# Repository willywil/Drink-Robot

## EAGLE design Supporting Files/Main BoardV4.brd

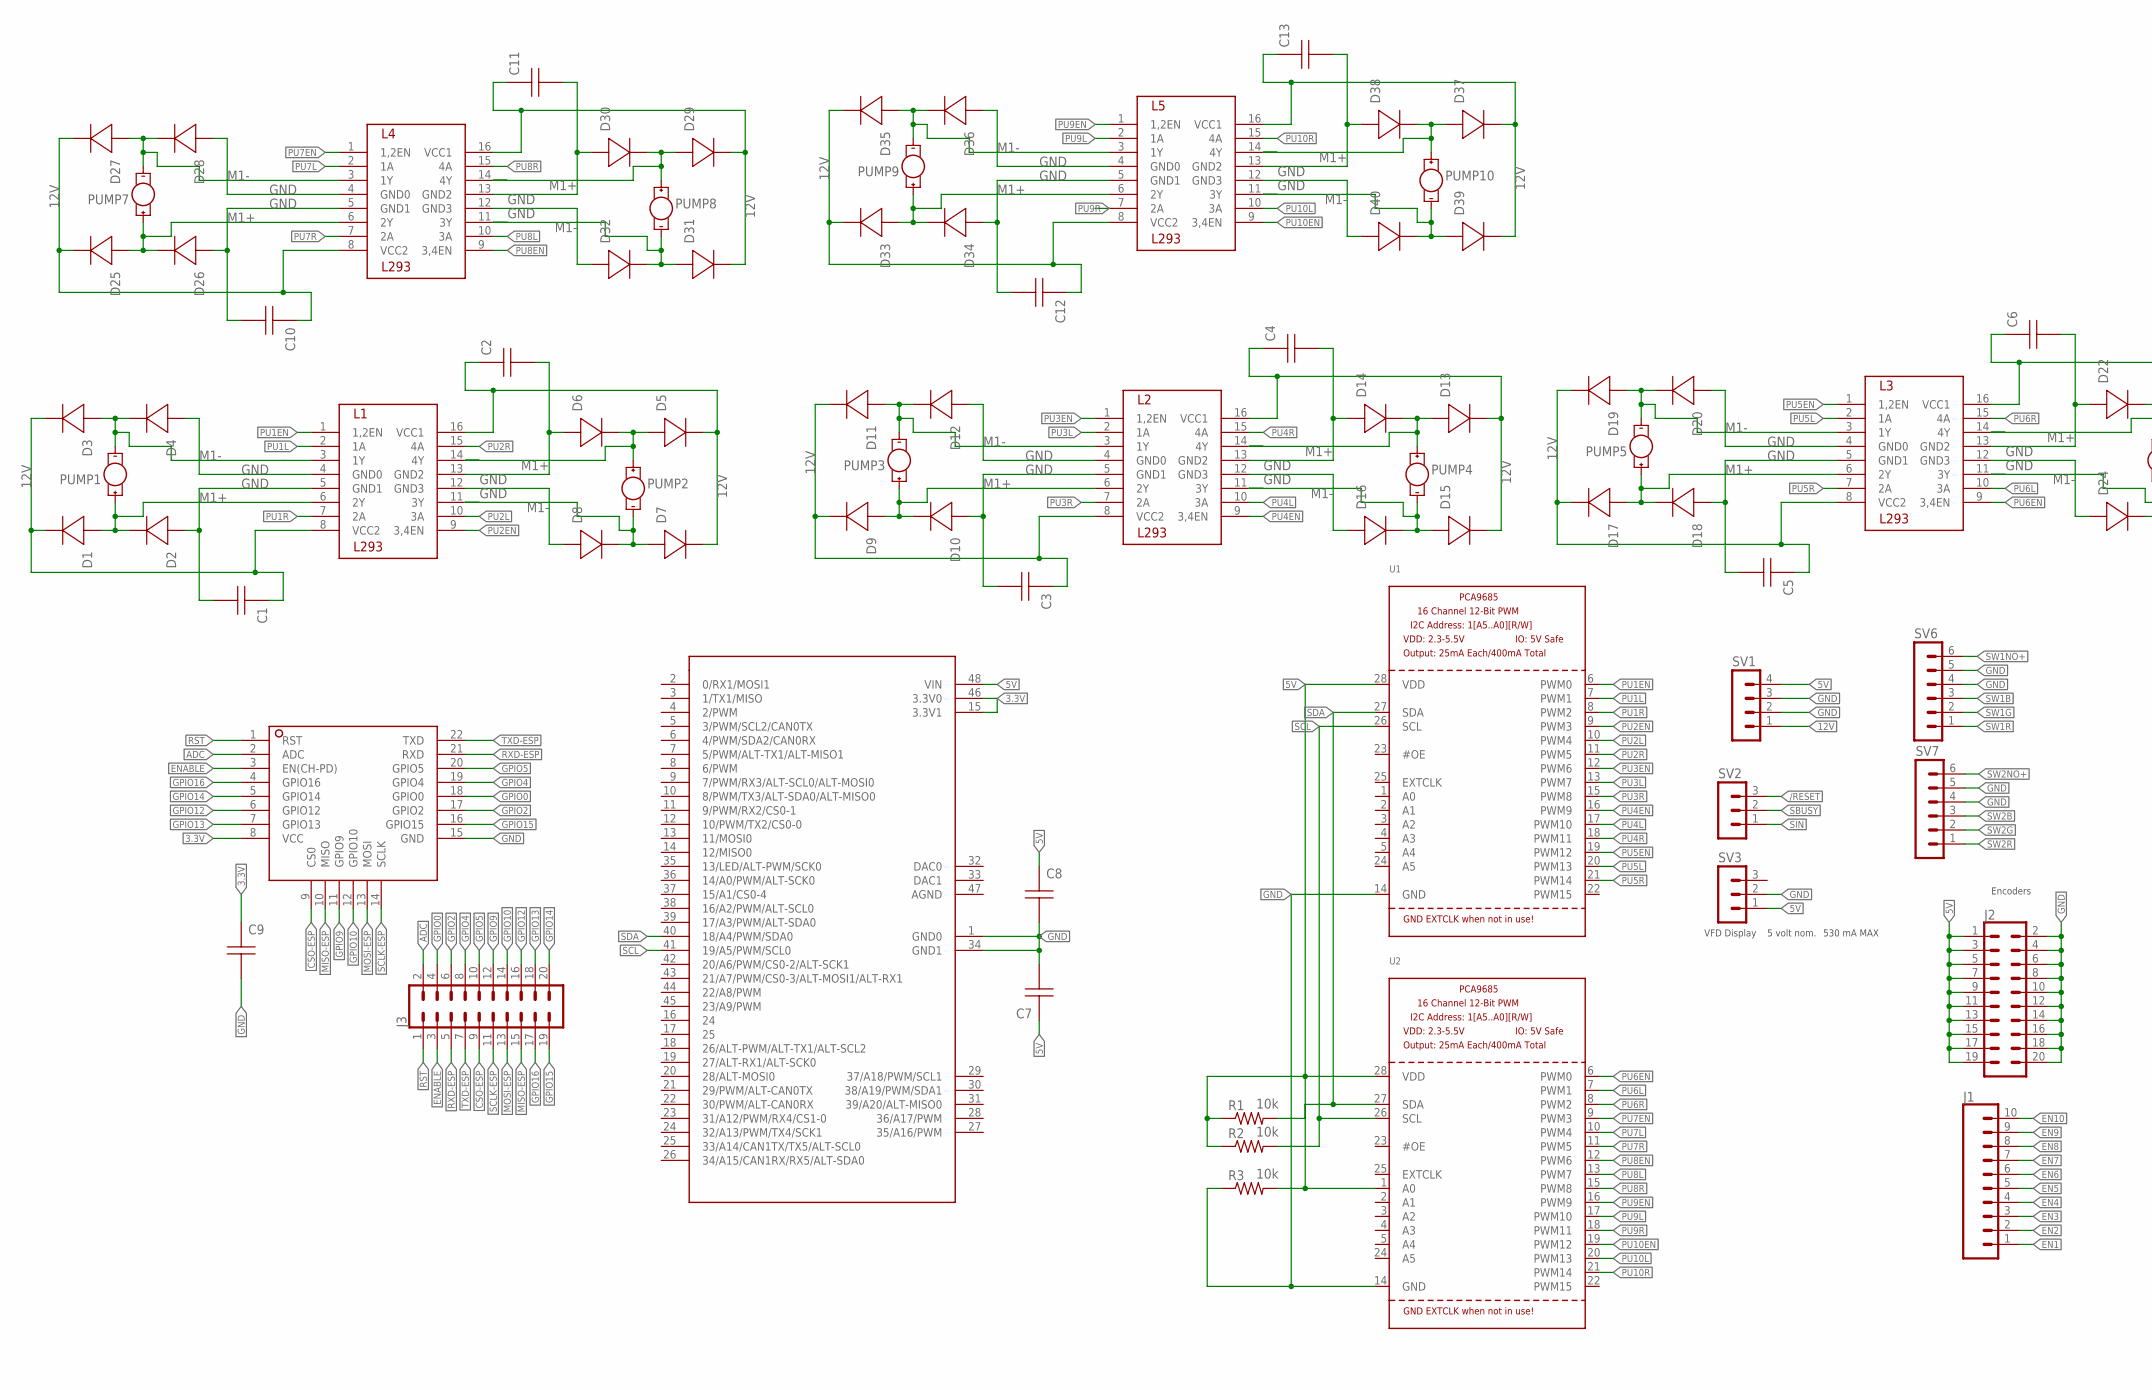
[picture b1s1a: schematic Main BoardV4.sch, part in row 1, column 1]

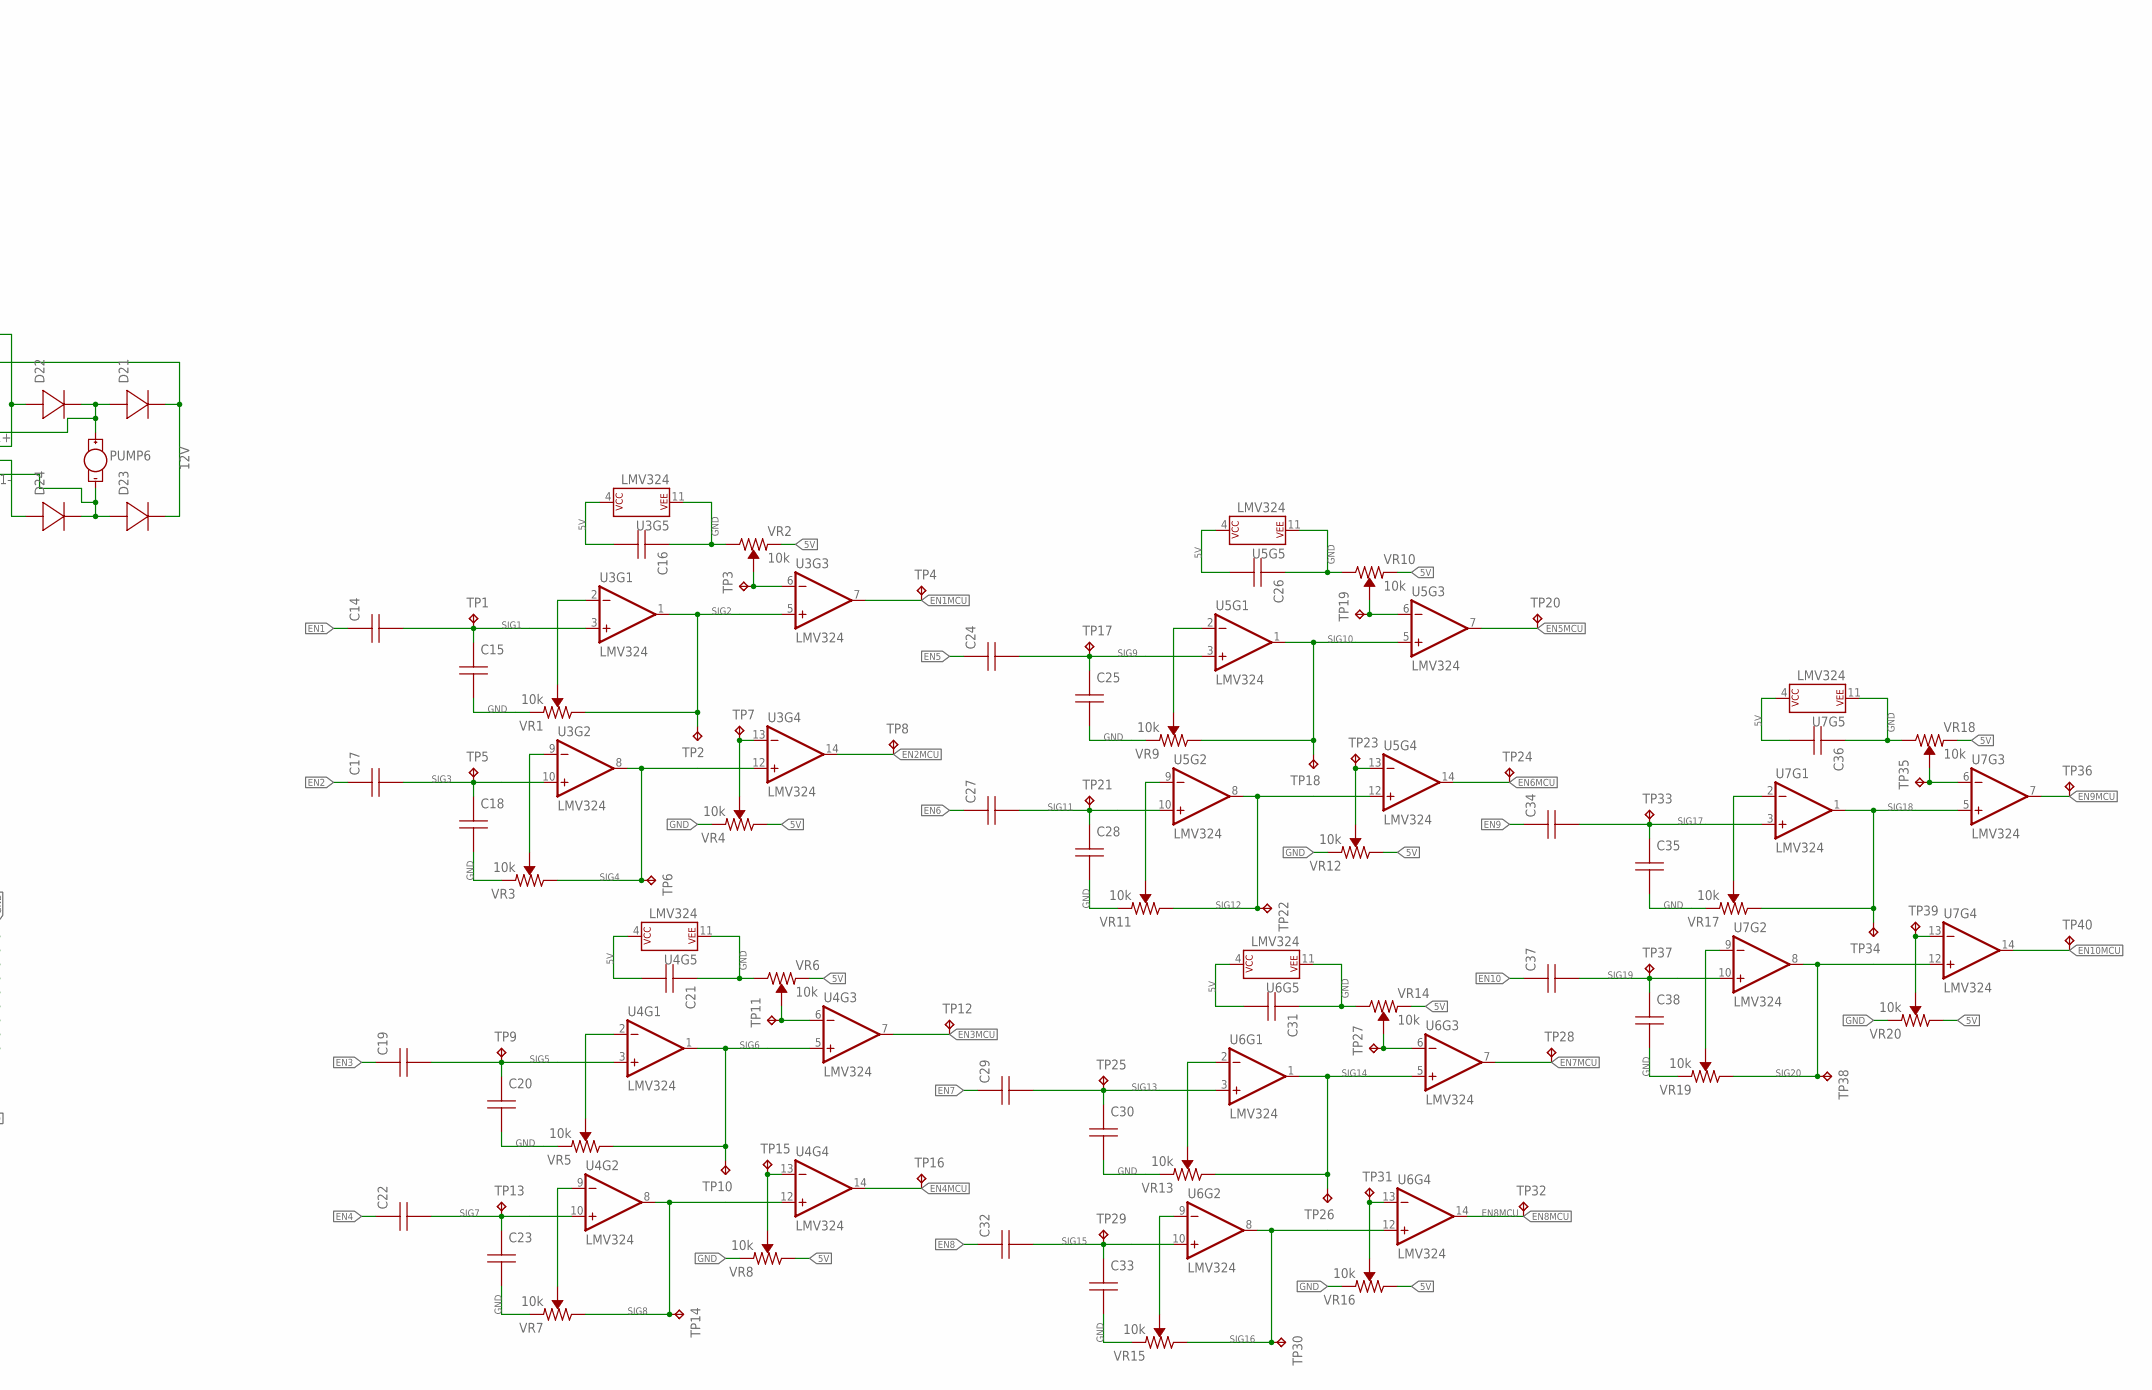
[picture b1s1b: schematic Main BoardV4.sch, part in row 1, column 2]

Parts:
C1, C2, C3, C4, C5, C6, C7, C8, C9, C10, C11, C12, C13, C14, C15, C16, C17, C18, C19, C20, C21, C22, C23, C24, C25, C26, C27, C28, C29, C30, C31, C32, C33, C34, C35, C36, C37, C38: CAP; C0805
D1, D2, D3, D4, D5, D6, D7, D8, D9, D10, D11, D12, D13, D14, D15, D16, D17, D18, D19, D20, D21, D22, D23, D24, D25, D26, D27, D28, D29, D30, D31, D32, D33, D34, D35, D36, D37, D38, D39, D40: UPR5E3-DIODE; DIOC4519X114
ESP1: ESP8266; ESP8266MOD
J1: CONN_10NO_SILK_PTH_FEMALE; 1X10_NO_SILK
J2: CONN_10X2NOSILK; 2X10_NOSILK
J3: CONN_10X22X10_LOCK; 2X10_LOCK
L1, L2, L3, L4, L5: L293; DIP762W53P254L1969H508Q16B
PUMP1, PUMP2, PUMP3, PUMP4, PUMP5, PUMP6, PUMP7, PUMP8, PUMP9, PUMP10: PUMPS; 1X2_HEADER
R1, R2, R3: 10k; R0402
SV1: MA04-1
SV2, SV3: MA03-1
SV6, SV7: MA06-1
TEENSY1: TEENSY_3.5; DIP1524W60P254L6350H635Q48A
TP1, TP2, TP3, TP4, TP5, TP6, TP7, TP8, TP9, TP10, TP11, TP12, TP13, TP14, TP15, TP16, TP17, TP18, TP19, TP20, TP21, TP22, TP23, TP24, TP25, TP26, TP27, TP28, TP29, TP30, TP31, TP32, TP33, TP34, TP35, TP36, TP37, TP38, TP39, TP40: TPPAD1-13; P1-13
U1, U2: PCA9685; TSSOP28
U3, U4, U5, U6, U7: LMV324; SO14
VR1, VR2, VR3, VR4, VR5, VR6, VR7, VR8, VR9, VR10, VR11, VR12, VR13, VR14, VR15, VR16, VR17, VR18, VR19, VR20: 10k; TRIMPOT-SMD-TC33X

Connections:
/RESET: SV2.3, TEENSY1.22 (30/PWM/ALT-CAN0RX)
ADC: ESP1.2 (ADC), J3.2
CSO-ESP: ESP1.9 (CS0), J3.9, TEENSY1.12 (10/PWM/TX2/CS0-0)
EN1: C14.1 (A), J1.1
EN1MCU: TEENSY1.36 (14/A0/PWM/ALT-SCK0), TP4.TP, U3.7 (OUT)
EN2: C17.1 (A), J1.2
EN2MCU: TEENSY1.37 (15/A1/CS0-4), TP8.TP, U3.14 (OUT)
EN3: C19.1 (A), J1.3
EN3MCU: TEENSY1.38 (16/A2/PWM/ALT-SCL0), TP12.TP, U4.7 (OUT)
EN4: C22.1 (A), J1.4
EN4MCU: TEENSY1.39 (17/A3/PWM/ALT-SDA0), TP16.TP, U4.14 (OUT)
EN5: C24.1 (A), J1.5
EN6: C27.1 (A), J1.6
EN7: C29.1 (A), J1.7
EN7MCU: TEENSY1.42 (20/A6/PWM/CS0-2/ALT-SCK1), TP28.TP, U6.7 (OUT)
EN8: C32.1 (A), J1.8
EN8MCU: TEENSY1.43 (21/A7/PWM/CS0-3/ALT-MOSI1/ALT-RX1), TP32.TP, U6.14 (OUT)
EN9: C34.1 (A), J1.9
EN9MCU: TEENSY1.44 (22/A8/PWM), TP36.TP, U7.7 (OUT)
EN10: C37.1 (A), J1.10
EN10MCU: TEENSY1.45 (23/A9/PWM), TP40.TP, U7.14 (OUT)
EN-WIFI: TEENSY1.24 (32/A13/PWM/TX4/SCK1); also elsewhere on the board
ENABLE: ESP1.3 (EN(CH-PD)), J3.3, TEENSY1.20 (28/ALT-MOSI0)
GND: C1.2 (B), C2.2 (B), C3.2 (B), C4.2 (B), C5.2 (B), C6.2 (B), C7.2 (B), C8.2 (B), C9.2 (B), C10.2 (B), C11.2 (B), C12.2 (B), C13.2 (B), C15.2 (B), C16.1 (A), C18.2 (B), C20.2 (B), C21.1 (A), C23.2 (B), C25.2 (B), C26.1 (A), C28.2 (B), C30.2 (B), C31.1 (A), C33.2 (B), C35.2 (B), C36.1 (A), C38.2 (B), D2.2 (+), D4.2 (+), D6.2 (+), D8.2 (+), D10.2 (+), D12.2 (+), D14.2 (+), D16.2 (+), D18.2 (+), D20.2 (+), D22.2 (+), D24.2 (+), D26.2 (+), D28.2 (+), D30.2 (+), D32.2 (+), D34.2 (+), D36.2 (+), D38.2 (+), D40.2 (+), ESP1.15 (GND), J2.2, J2.4, J2.6, J2.8, J2.10, J2.12, J2.14, J2.16, J2.18, J2.20, L1.4 (GND0), L1.5 (GND1), L1.12 (GND3), L1.13 (GND2), L2.4 (GND0), L2.5 (GND1), L2.12 (GND3), L2.13 (GND2), L3.4 (GND0), L3.5 (GND1), L3.12 (GND3), L3.13 (GND2), L4.4 (GND0), L4.5 (GND1), L4.12 (GND3), L4.13 (GND2), L5.4 (GND0), L5.5 (GND1), L5.12 (GND3), L5.13 (GND2), R3.1, SV1.2, SV1.3, SV3.2, SV6.4, SV6.5, SV7.4, SV7.5, TEENSY1.1 (GND0), TEENSY1.34 (GND1), U1.14 (GND), U2.14 (GND), U3.11 (P$V-), U4.11 (P$V-), U5.11 (P$V-), U6.11 (P$V-), U7.11 (P$V-), VR1.3 (CCW), VR2.1 (CW), VR3.3 (CCW), VR4.3 (CCW), VR5.3 (CCW), VR6.1 (CW), VR7.3 (CCW), VR8.3 (CCW), VR9.3 (CCW), VR10.1 (CW), VR11.3 (CCW), VR12.3 (CCW), VR13.3 (CCW), VR14.1 (CW), VR15.3 (CCW), VR16.3 (CCW), VR17.3 (CCW), VR18.1 (CW), VR19.3 (CCW), VR20.3 (CCW); also elsewhere on the board
GPIO0: ESP1.18 (GPIO0), J3.4, TEENSY1.23 (31/A12/PWM/RX4/CS1-0); also elsewhere on the board
GPIO2: ESP1.17 (GPIO2), J3.6
GPIO4: ESP1.19 (GPIO4), J3.8
GPIO5: ESP1.20 (GPIO5), J3.10
GPIO9: ESP1.11 (GPIO9), J3.12
GPIO10: ESP1.12 (GPIO10), J3.14
GPIO12: ESP1.6 (GPIO12), J3.16
GPIO13: ESP1.7 (GPIO13), J3.18, TEENSY1.19 (27/ALT-RX1/ALT-SCK0)
GPIO14: ESP1.5 (GPIO14), J3.20
GPIO15: ESP1.16 (GPIO15), J3.19, TEENSY1.18 (26/ALT-PWM/ALT-TX1/ALT-SCL2)
GPIO16: ESP1.4 (GPIO16), J3.17
MISO-ESP: ESP1.10 (MISO), J3.15, TEENSY1.14 (12/MISO0)
MOSI-ESP: ESP1.13 (MOSI), J3.13, TEENSY1.13 (11/MOSI0)
unnamed: U4.2 (-IN), VR5.2 (WIPER)
unnamed: U3.2 (-IN), VR1.2 (WIPER)
unnamed: TP11.TP, U4.6 (-IN), VR6.2 (WIPER)
unnamed: U4.9 (-IN), VR7.2 (WIPER)
unnamed: TP15.TP, U4.13 (-IN), VR8.2 (WIPER)
unnamed: U5.2 (-IN), VR9.2 (WIPER)
unnamed: TP3.TP, U3.6 (-IN), VR2.2 (WIPER)
unnamed: TP19.TP, U5.6 (-IN), VR10.2 (WIPER)
unnamed: U5.9 (-IN), VR11.2 (WIPER)
unnamed: TP23.TP, U5.13 (-IN), VR12.2 (WIPER)
unnamed: U3.9 (-IN), VR3.2 (WIPER)
unnamed: TP7.TP, U3.13 (-IN), VR4.2 (WIPER)
unnamed: U6.2 (-IN), VR13.2 (WIPER)
unnamed: TP27.TP, U6.6 (-IN), VR14.2 (WIPER)
unnamed: U6.9 (-IN), VR15.2 (WIPER)
unnamed: TP31.TP, U6.13 (-IN), VR16.2 (WIPER)
unnamed: U7.2 (-IN), VR17.2 (WIPER)
unnamed: TP35.TP, U7.6 (-IN), VR18.2 (WIPER)
unnamed: U7.9 (-IN), VR19.2 (WIPER)
unnamed: TP39.TP, U7.13 (-IN), VR20.2 (WIPER)
PU1EN: L1.1 (1,2EN), U1.6 (PWM0)
PU1L: L1.2 (1A), U1.7 (PWM1)
PU1R: L1.7 (2A), U1.8 (PWM2)
PU2EN: L1.9 (3,4EN), U1.9 (PWM3)
PU2L: L1.10 (3A), U1.10 (PWM4)
PU2R: L1.15 (4A), U1.11 (PWM5)
PU3EN: L2.1 (1,2EN), U1.12 (PWM6)
PU3L: L2.2 (1A), U1.13 (PWM7)
PU3R: L2.7 (2A), U1.15 (PWM8)
PU4EN: L2.9 (3,4EN), U1.16 (PWM9)
PU4L: L2.10 (3A), U1.17 (PWM10)
PU4R: L2.15 (4A), U1.18 (PWM11)
PU5EN: L3.1 (1,2EN), U1.19 (PWM12)
PU5L: L3.2 (1A), U1.20 (PWM13)
PU5R: L3.7 (2A), U1.21 (PWM14)
PU6EN: L3.9 (3,4EN), U2.6 (PWM0)
PU6L: L3.10 (3A), U2.7 (PWM1)
PU6R: L3.15 (4A), U2.8 (PWM2)
PU7EN: L4.1 (1,2EN), U2.9 (PWM3)
PU7L: L4.2 (1A), U2.10 (PWM4)
PU7R: L4.7 (2A), U2.11 (PWM5)
PU8EN: L4.9 (3,4EN), U2.12 (PWM6)
PU8L: L4.10 (3A), U2.13 (PWM7)
PU8R: L4.15 (4A), U2.15 (PWM8)
PU9EN: L5.1 (1,2EN), U2.16 (PWM9)
PU9L: L5.2 (1A), U2.17 (PWM10)
PU9R: L5.7 (2A), U2.18 (PWM11)
PU10EN: L5.9 (3,4EN), U2.19 (PWM12)
PU10L: L5.10 (3A), U2.20 (PWM13)
PU10R: L5.15 (4A), U2.21 (PWM14)
RST: ESP1.1 (RST), J3.1, TEENSY1.21 (29/PWM/ALT-CAN0TX); also elsewhere on the board
RXD-ESP: ESP1.21 (RXD), J3.5, TEENSY1.3 (1/TX1/MISO)
SBUSY: SV2.2, TEENSY1.11 (9/PWM/RX2/CS0-1)
SCLK-ESP: ESP1.14 (SCLK), J3.11, TEENSY1.35 (13/LED/ALT-PWM/SCK0)
SIG1: C14.2 (B), C15.1 (A), TP1.TP, U3.3 (+IN)
SIG2: TP2.TP, U3.1 (OUT), U3.5 (+IN), VR1.1 (CW)
SIG3: C17.2 (B), C18.1 (A), TP5.TP, U3.10 (+IN)
SIG4: TP6.TP, U3.8 (OUT), U3.12 (+IN), VR3.1 (CW)
SIG5: C19.2 (B), C20.1 (A), TP9.TP, U4.3 (+IN)
SIG6: TP10.TP, U4.1 (OUT), U4.5 (+IN), VR5.1 (CW)
SIG7: C22.2 (B), C23.1 (A), TP13.TP, U4.10 (+IN)
SIG8: TP14.TP, U4.8 (OUT), U4.12 (+IN), VR7.1 (CW)
SIG9: C24.2 (B), C25.1 (A), TP17.TP, U5.3 (+IN)
SIG10: TP18.TP, U5.1 (OUT), U5.5 (+IN), VR9.1 (CW)
SIG11: C27.2 (B), C28.1 (A), TP21.TP, U5.10 (+IN)
SIG12: TP22.TP, U5.8 (OUT), U5.12 (+IN), VR11.1 (CW)
SIG13: C29.2 (B), C30.1 (A), TP25.TP, U6.3 (+IN)
SIG14: TP26.TP, U6.1 (OUT), U6.5 (+IN), VR13.1 (CW)
SIG15: C32.2 (B), C33.1 (A), TP29.TP, U6.10 (+IN)
SIG16: TP30.TP, U6.8 (OUT), U6.12 (+IN), VR15.1 (CW)
SIG17: C34.2 (B), C35.1 (A), TP33.TP, U7.3 (+IN)
SIG18: TP34.TP, U7.1 (OUT), U7.5 (+IN), VR17.1 (CW)
SIG19: C37.2 (B), C38.1 (A), TP37.TP, U7.10 (+IN)
SIG20: TP38.TP, U7.8 (OUT), U7.12 (+IN), VR19.1 (CW)
SIN: SV2.1, TEENSY1.10 (8/PWM/TX3/ALT-SDA0/ALT-MISO0)
SW1B: SV6.3, TEENSY1.6 (4/PWM/SDA2/CAN0RX)
SW1G: SV6.2, TEENSY1.5 (3/PWM/SCL2/CAN0TX)
SW1NO+: SV6.6, TEENSY1.16 (24)
SW1R: SV6.1, TEENSY1.4 (2/PWM)
SW2B: SV7.3, TEENSY1.9 (7/PWM/RX3/ALT-SCL0/ALT-MOSI0)
SW2G: SV7.2, TEENSY1.8 (6/PWM)
SW2NO+: SV7.6, TEENSY1.17 (25)
SW2R: SV7.1, TEENSY1.7 (5/PWM/ALT-TX1/ALT-MISO1)
TXD-ESP: ESP1.22 (TXD), J3.7, TEENSY1.2 (0/RX1/MOSI1)

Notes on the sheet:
VFD Display
5 volt nom.
530 mA MAX
Encoders

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
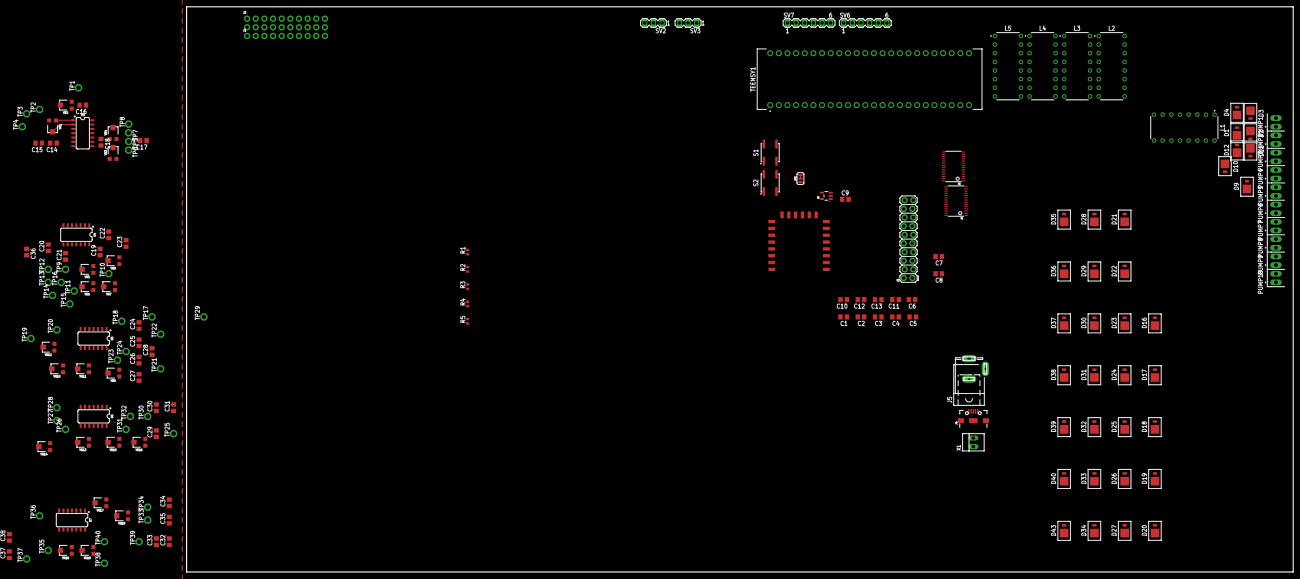
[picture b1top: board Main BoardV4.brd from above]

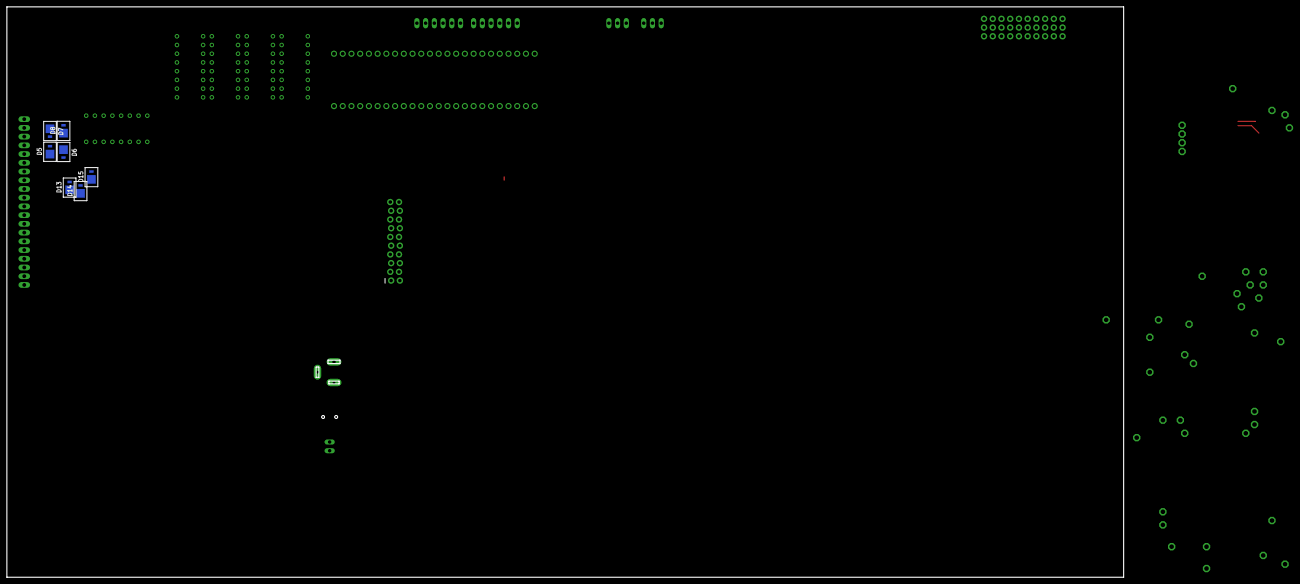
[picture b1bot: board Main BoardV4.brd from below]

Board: 2 copper layers, 325.1 x 166.0 mm, 182 parts (7 on the bottom side), 153 nets.

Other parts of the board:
D43: UPR5E3-DIODE; DIOC4519X114
J4: USB-B-MICRO-SMD
J5: SPC4077
JP1: JUMPER-SMT_3_1-NC_TRACE_SILK; SMT-JUMPER_3_1-NC_TRACE_SILK
R4, R5: 10k; R0402
S1, S2: BUTTON; SOT370P645X154-4
U8: 3.3V; SOT23-5
X1: 22-23-2021

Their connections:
D+: J4.D+, X1.1
D-: J4.D-, X1.2
EN-WIFI: JP1.1; also elsewhere on the board
GND: D43.2, J4.GND, J4.SHIELD1, J4.SHIELD2, J4.SHIELD3, J5.1, J5.2, U8.2; also elsewhere on the board
GPIO0: R5.2, S2.1, S2.2; also elsewhere on the board
unnamed: JP1.2, U8.3
unnamed: S1.3, S1.4, S2.3, S2.4
RST: R4.2, S1.1, S1.2; also elsewhere on the board

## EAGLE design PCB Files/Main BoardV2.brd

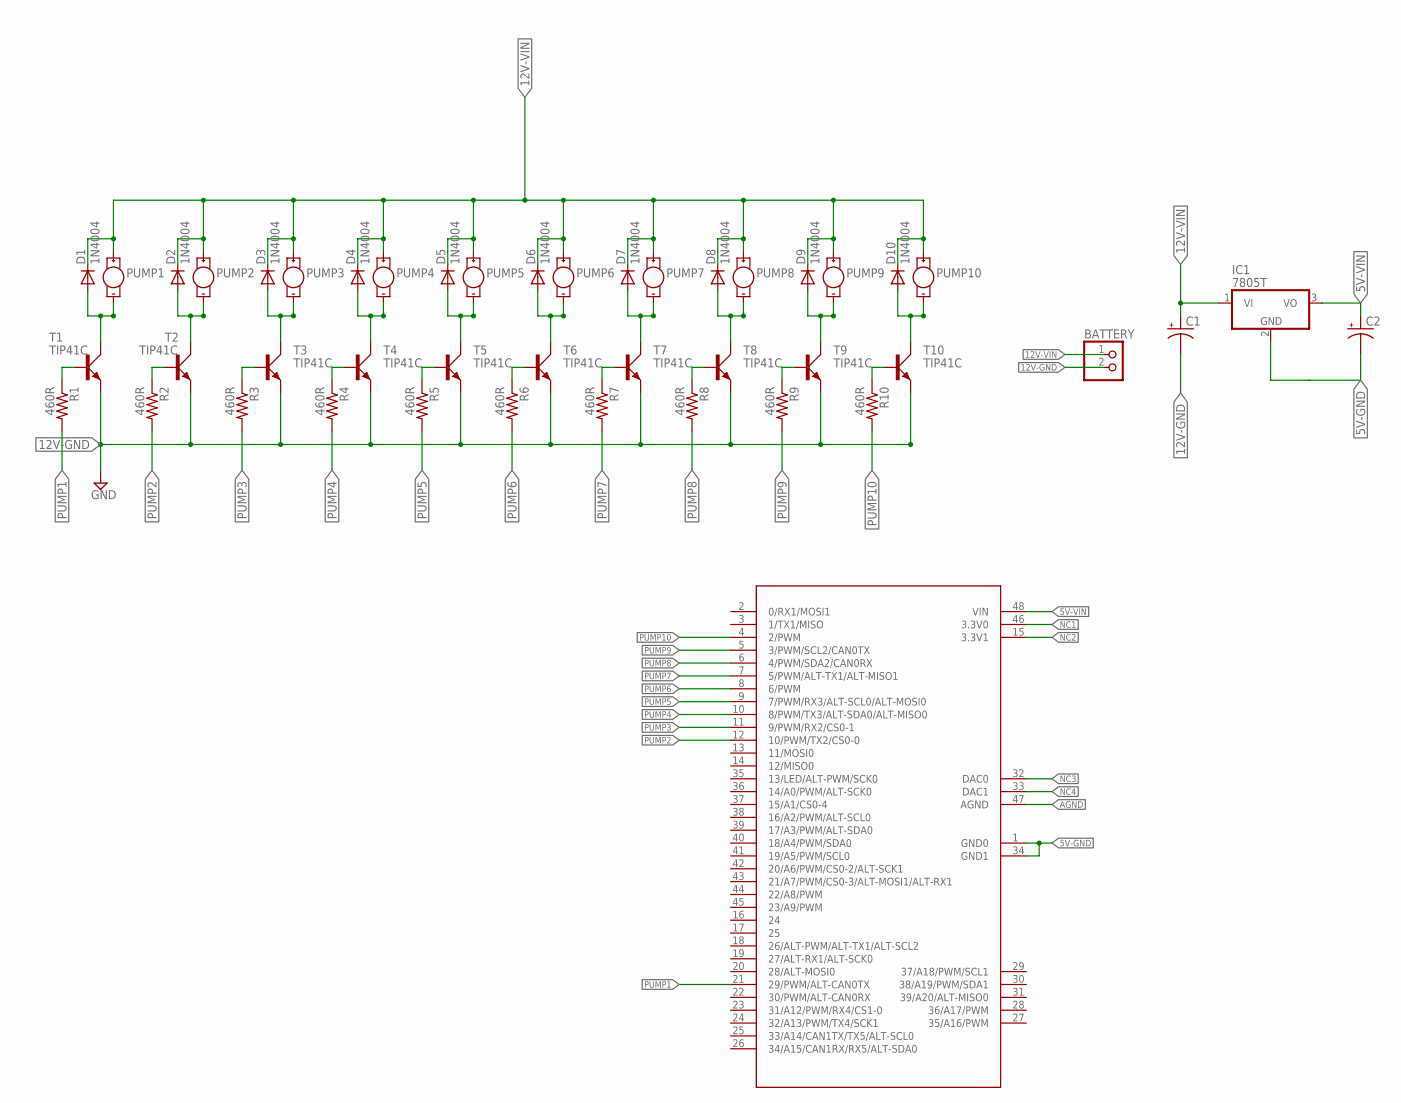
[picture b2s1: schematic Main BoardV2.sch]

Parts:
BATTERY: PINHD-1X2; 1X02
C1: CPOL-USE5-10.5; E5-10,5
C2: CPOL-USE2.5-5; E2,5-5
D1, D2, D3, D4, D5, D6, D7, D8, D9, D10: 1N4004; DO41-10
IC1: 7805T; TO220H
PUMP1, PUMP2, PUMP3, PUMP4, PUMP5, PUMP6, PUMP7, PUMP8, PUMP9, PUMP10: PUMPS; 1X2_HEADER
R1, R2, R3, R4, R5, R6, R7, R8, R9, R10: 460R; 0805-THM
T1, T2, T3, T4, T5, T6, T7, T8, T9, T10: TIP41C; TO220AV
TEENSY1: TEENSY_3.5; DIP1524W60P254L6350H635Q48A

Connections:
5V-GND: C2.-, IC1.2 (GND), TEENSY1.1 (GND0), TEENSY1.34 (GND1)
5V-VIN: C2.+, IC1.3 (VO), TEENSY1.48 (VIN)
12V-GND: BATTERY.2, C1.-, T1.E, T2.E, T3.E, T4.E, T5.E, T6.E, T7.E, T8.E, T9.E, T10.E
12V-VIN: BATTERY.1, C1.+, D1.C, D2.C, D3.C, D4.C, D5.C, D6.C, D7.C, D8.C, D9.C, D10.C, IC1.1 (VI), PUMP1.1 (+), PUMP2.1 (+), PUMP3.1 (+), PUMP4.1 (+), PUMP5.1 (+), PUMP6.1 (+), PUMP7.1 (+), PUMP8.1 (+), PUMP9.1 (+), PUMP10.1 (+)
AGND: TEENSY1.47 (AGND)
unnamed: D10.A, PUMP10.2 (-), T10.C
unnamed: D9.A, PUMP9.2 (-), T9.C
unnamed: D8.A, PUMP8.2 (-), T8.C
unnamed: D7.A, PUMP7.2 (-), T7.C
unnamed: D6.A, PUMP6.2 (-), T6.C
unnamed: D5.A, PUMP5.2 (-), T5.C
unnamed: D4.A, PUMP4.2 (-), T4.C
unnamed: D3.A, PUMP3.2 (-), T3.C
unnamed: D2.A, PUMP2.2 (-), T2.C
unnamed: D1.A, PUMP1.2 (-), T1.C
unnamed: R1.1, T1.B
unnamed: R2.1, T2.B
unnamed: R3.1, T3.B
unnamed: R4.1, T4.B
unnamed: R5.1, T5.B
unnamed: R6.1, T6.B
unnamed: R7.1, T7.B
unnamed: R8.1, T8.B
unnamed: R9.1, T9.B
unnamed: R10.1, T10.B
NC1: TEENSY1.46 (3.3V0)
NC2: TEENSY1.15 (3.3V1)
NC3: TEENSY1.32 (DAC0)
NC4: TEENSY1.33 (DAC1)
PUMP1: R1.2, TEENSY1.21 (29/PWM/ALT-CAN0TX)
PUMP2: R2.2, TEENSY1.12 (10/PWM/TX2/CS0-0)
PUMP3: R3.2, TEENSY1.11 (9/PWM/RX2/CS0-1)
PUMP4: R4.2, TEENSY1.10 (8/PWM/TX3/ALT-SDA0/ALT-MISO0)
PUMP5: R5.2, TEENSY1.9 (7/PWM/RX3/ALT-SCL0/ALT-MOSI0)
PUMP6: R6.2, TEENSY1.8 (6/PWM)
PUMP7: R7.2, TEENSY1.7 (5/PWM/ALT-TX1/ALT-MISO1)
PUMP8: R8.2, TEENSY1.6 (4/PWM/SDA2/CAN0RX)
PUMP9: R9.2, TEENSY1.5 (3/PWM/SCL2/CAN0TX)
PUMP10: R10.2, TEENSY1.4 (2/PWM)

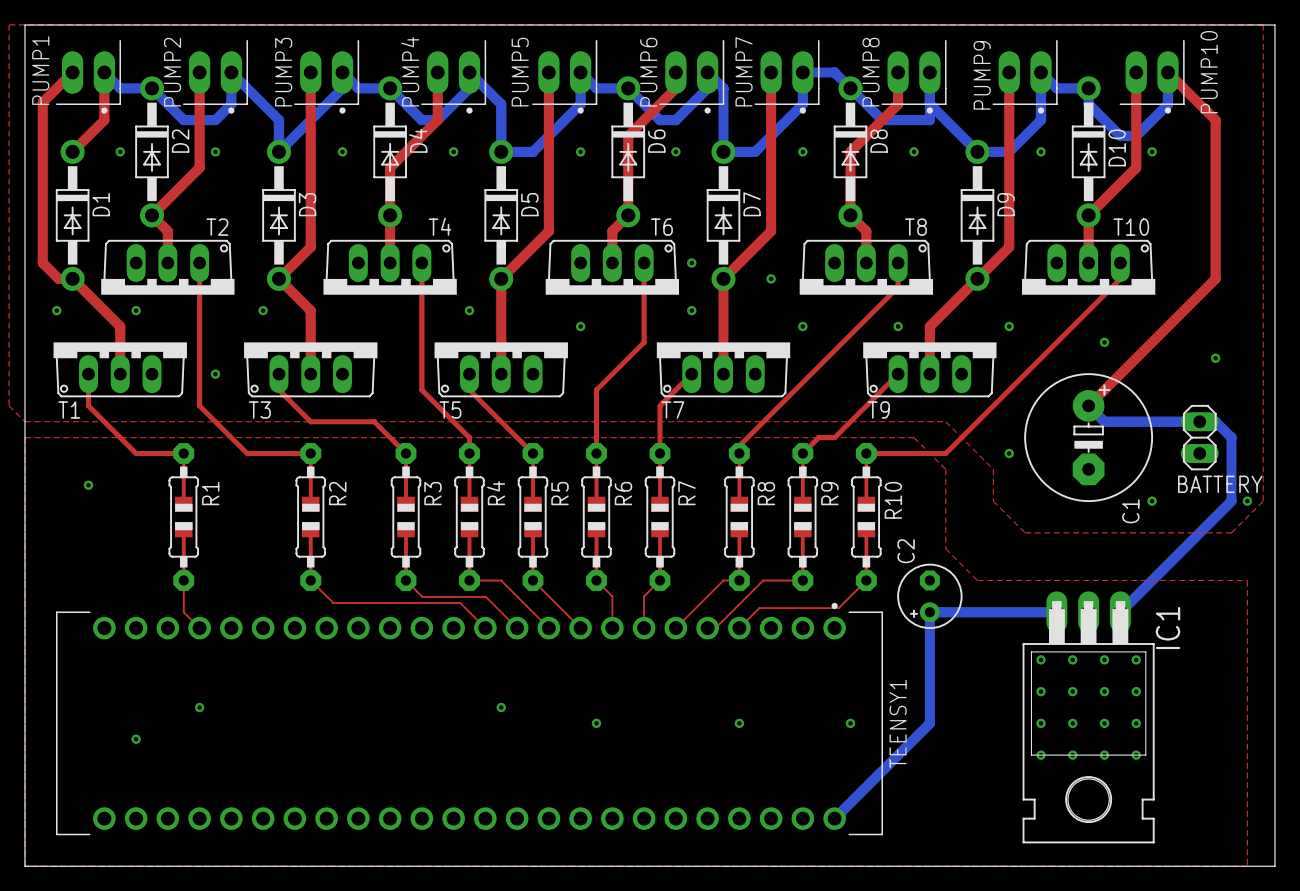
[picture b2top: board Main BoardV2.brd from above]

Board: 2 copper layers, 100.0 x 67.3 mm, 45 parts (0 on the bottom side), 34 nets.

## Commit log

2018-09-04 Brought all the major components together
    Added l293 motor controller, esp module, encoder circuit, and all supporting curcuitry
2018-09-07 Finished schematic
    Need to layout pcb

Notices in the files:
parts and their libraries:
SparkFun-Connectors: Licensing: Creative Commons ShareAlike 4.0 International - https://creativecommons.org/licenses/by-sa/4.0
